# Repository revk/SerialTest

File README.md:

# ESP32-HelloWorld

Start for ESP32-RevK builds
# SerialTest

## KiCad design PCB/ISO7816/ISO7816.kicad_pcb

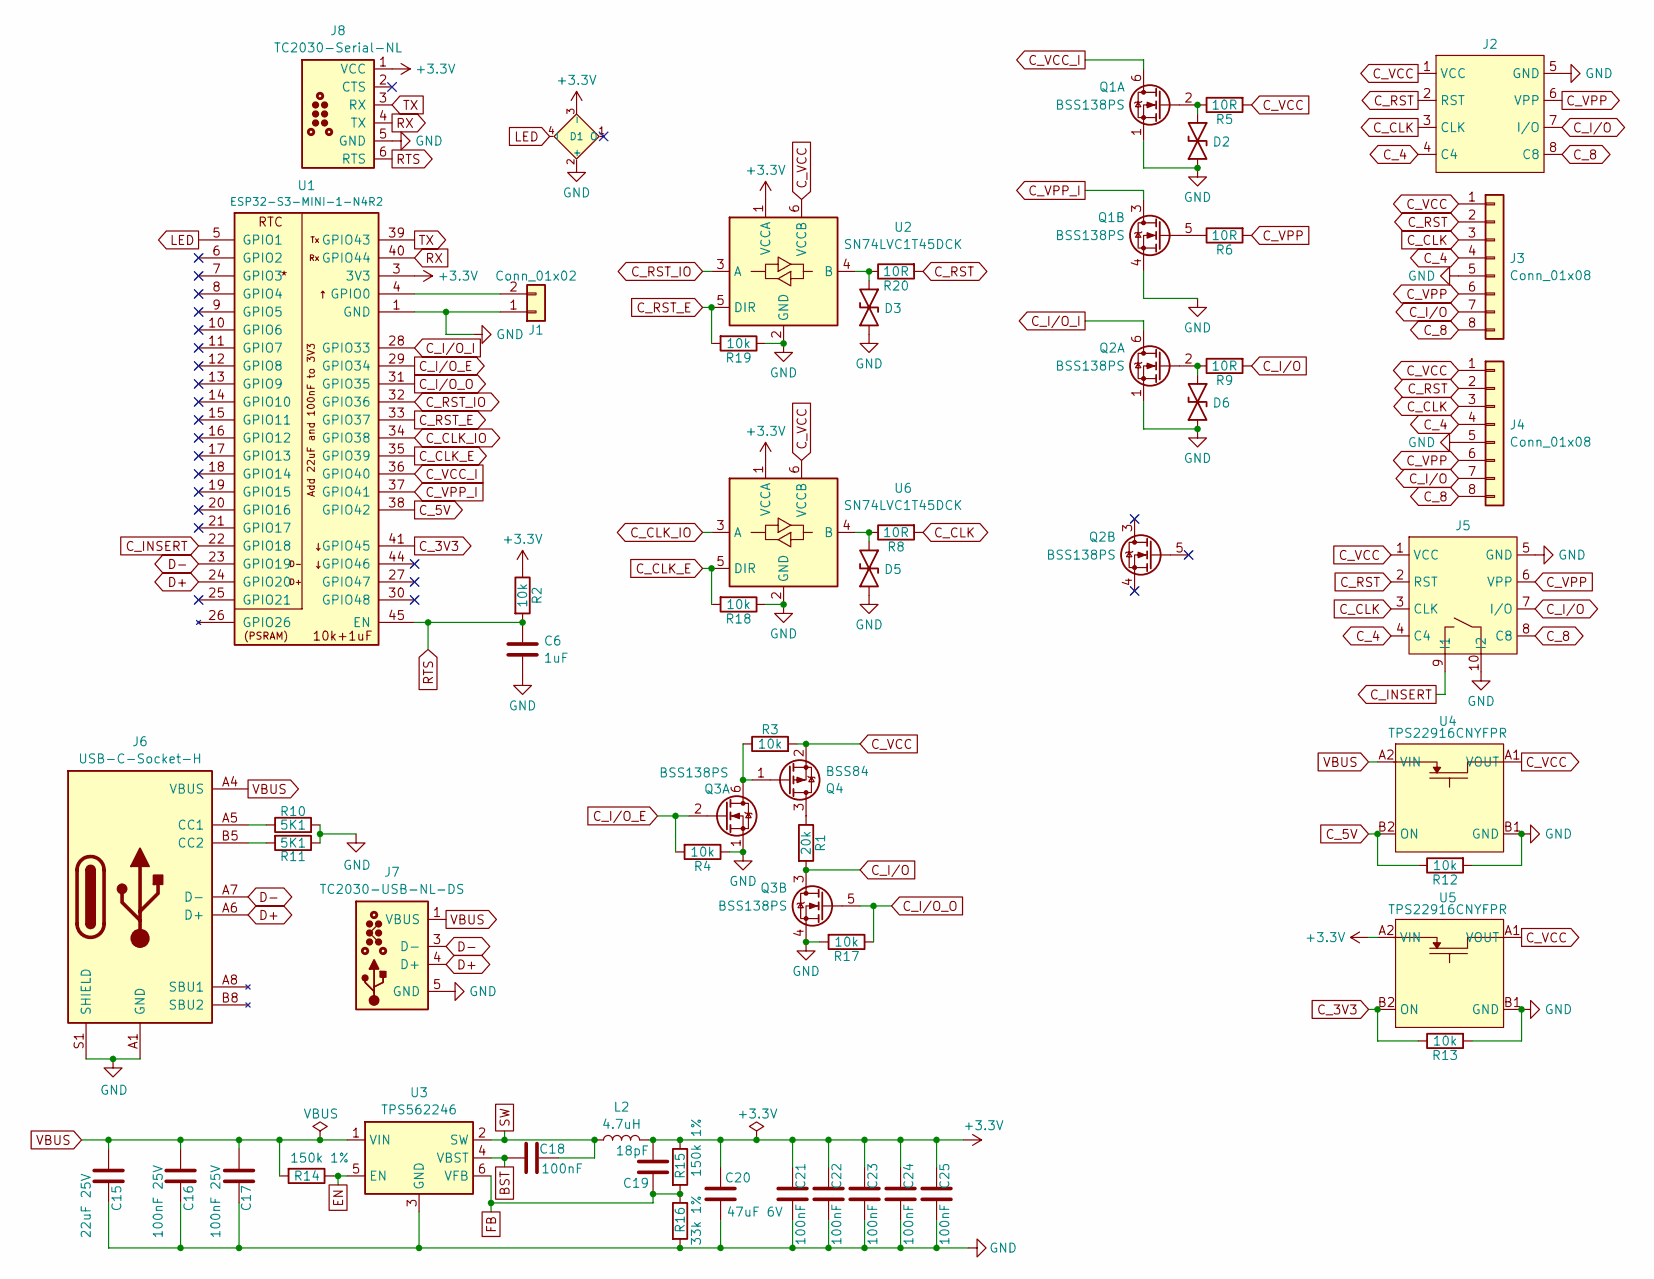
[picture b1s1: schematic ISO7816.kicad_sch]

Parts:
C6: 1uF; C_0201
C15: 22uF 25V; C_0805; MPN C45783
C16, C17: 100nF 25V; C_0402; MPN C56392
C18, C21, C22, C23, C24, C25: 100nF; C_0201; MPN C76934
C19: 18pF; C_0201; MPN C62164
C20: 47uF 6V; C_0805; MPN C16780
D1: XL-1010RGBC-WS2812B; SMD1010; MPN C5349953; LCSC Part # C5349953
D2, D3, D5, D6: DFN1006-2L; MPN C5137770; LCSC Part # C5137770
J1: Conn_01x02; AA-Pad
J2: ISO7816
J3, J4: Conn_01x08; PinHeader_1x08_P2.54mm_Vertical
J5: 7434L0825S01LF
J6: USB-C-Socket-H; MPN C709357
J7: TC2030-USB-NL-DS; Tag-Connect_TC2030-IDC-NL_2x03_P1.27mm_Vertical
J8: TC2030-Serial-NL; Tag-Connect_TC2030-IDC-NL_2x03_P1.27mm_Vertical
L2: 4.7uH; L_5x5; MPN C307876
Q1, Q2, Q3: BSS138PS; SOT-363_SC-70-6; MPN C193381; LCSC Part # C193381
Q4: BSS84; SOT-23
R1: 20k; R_0201
R2, R3, R4, R12, R13, R17, R18, R19: 10k; R_0201
R5, R6, R8, R9, R20: 10R; R_0201
R10, R11: 5K1; R_0201; MPN C274341
R14, R15: 150k 1%; R_0201; MPN C310173
R16: 33k 1%; R_0201; MPN C320835
U1: ESP32-S3-MINI-1-N4R2; ESP32-S3-MINI-1; MPN C3013941; LCSC Part # C3013941
U2, U6: SN74LVC1T45DCK; SOT-363_SC-70-6
U3: TPS562246; SOT-563; MPN C41833479
U4, U5: TPS22916CNYFPR; WCSP-4-0.78x0.78; MPN C2655476

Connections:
+3.3V: C19.2, C20.1, C21.2, C22.2, C23.2, C24.2, C25.2, D1.3 (-), J8.1 (VCC), L2.2, R2.1, R15.1, U1.3 (3V3), U2.1 (VCCA), U5.A2 (VIN), U6.1 (VCCA)
BST: C18.1, U3.4 (VBST)
C_3V3: R13.1, U1.41 (GPIO45), U5.B2 (ON)
C_4: J2.4 (C4), J3.4, J4.4, J5.4 (C4)
C_5V: R12.1, U1.38 (GPIO42), U4.B2 (ON)
C_8: J2.8 (C8), J3.8, J4.8, J5.8 (C8)
C_CLK: J2.3 (CLK), J3.3, J4.3, J5.3 (CLK), R8.2
C_CLK_E: R18.2, U1.35 (GPIO39), U6.5 (DIR)
C_CLK_IO: U1.34 (GPIO38), U6.3 (A)
C_INSERT: J5.9 (I1), U1.22 (GPIO18)
C_I/O: J2.7 (I/O), J3.7, J4.7, J5.7 (I/O), Q3.3 (SP), R1.2, R9.2
C_I/O_E: Q3.2 (GN), R4.2, U1.29 (GPIO34)
C_I/O_I: Q2.6 (DN), U1.28 (GPIO33)
C_I/O_O: Q3.5 (GP), R17.1, U1.31 (GPIO35)
C_RST: J2.2 (RST), J3.2, J4.2, J5.2 (RST), R20.2
C_RST_E: R19.2, U1.33 (GPIO37), U2.5 (DIR)
C_RST_IO: U1.32 (GPIO36), U2.3 (A)
C_VCC: J2.1 (VCC), J3.1, J4.1, J5.1 (VCC), Q4.2 (S), R3.2, R5.2, U2.6 (VCCB), U4.A1 (VOUT), U5.A1 (VOUT), U6.6 (VCCB)
C_VCC_I: Q1.6 (DN), U1.36 (GPIO40)
C_VPP: J2.6 (VPP), J3.6, J4.6, J5.6 (VPP), R6.2
C_VPP_I: Q1.3 (SP), U1.37 (GPIO41)
D+: J6.A6 (D+), J6.B6 (D+), J7.4 (D+), U1.24 (GPIO20)
D-: J6.A7 (D-), J6.B7 (D-), J7.2 (NC), J7.3 (D-), J7.6 (NC), U1.23 (GPIO19)
EN: R14.1, U3.5 (EN)
FB: C19.1, R15.2, R16.1, U3.6 (VFB)
GND: C6.2, C15.2, C16.2, C17.2, C20.2, C21.1, C22.1, C23.1, C24.1, C25.1, D1.2 (+), D2.1, D3.1, D5.1, D6.1, J1.1, J2.5 (GND), J3.5, J4.5, J5.5 (GND), J5.10 (I2), J6.A1 (GND), J6.A12 (GND), J6.B1 (GND), J6.B12 (GND), J6.S1 (SHIELD), J7.5 (GND), J8.5 (GND), Q1.1 (SN), Q1.4 (DP), Q2.1 (SN), Q3.1 (SN), Q3.4 (DP), R4.1, R10.2, R11.1, R12.2, R13.2, R16.2, R17.2, R18.1, R19.1, U1.1 (GND), U1.2 (GND), U1.42 (GND), U1.43 (GND), U1.46 (GND), U1.47 (GND), U1.48 (GND), U1.49 (GND), U1.50 (GND), U1.51 (GND), U1.52 (GND), U1.53 (GND), U1.54 (GND), U1.55 (GND), U1.56 (GND), U1.57 (GND), U1.58 (GND), U1.59 (GND), U1.60 (GND), U1.61 (GND), U1.62 (GND), U1.63 (GND), U1.64 (GND), U1.65 (GND), U2.2 (GND), U3.3 (GND), U4.B1 (GND), U5.B1 (GND), U6.2 (GND)
LED: D1.4 (I), U1.5 (GPIO1)
unnamed: J1.2, U1.4 (GPIO0)
unnamed: J6.A5 (CC1), R10.1
unnamed: J6.B5 (CC2), R11.2
unnamed: D2.2, Q1.2 (GN), R5.1
unnamed: Q1.5 (GP), R6.1
unnamed: D6.2, Q2.2 (GN), R9.1
unnamed: Q3.6 (DN), Q4.1 (G), R3.1
unnamed: Q4.3 (D), R1.1
unnamed: D3.2, R20.1, U2.4 (B)
unnamed: D5.2, R8.1, U6.4 (B)
RTS: C6.1, J8.6 (RTS), R2.2, U1.45 (EN)
RX: J8.4 (TX), U1.40 (GPIO44)
SW: C18.2, L2.1, U3.2 (SW)
TX: J8.3 (RX), U1.39 (GPIO43)
VBUS: C15.1, C16.1, C17.1, J6.A4 (VBUS), J6.A9 (VBUS), J6.B4 (VBUS), J6.B9 (VBUS), J7.1 (VBUS), R14.2, U3.1 (VIN), U4.A2 (VIN)

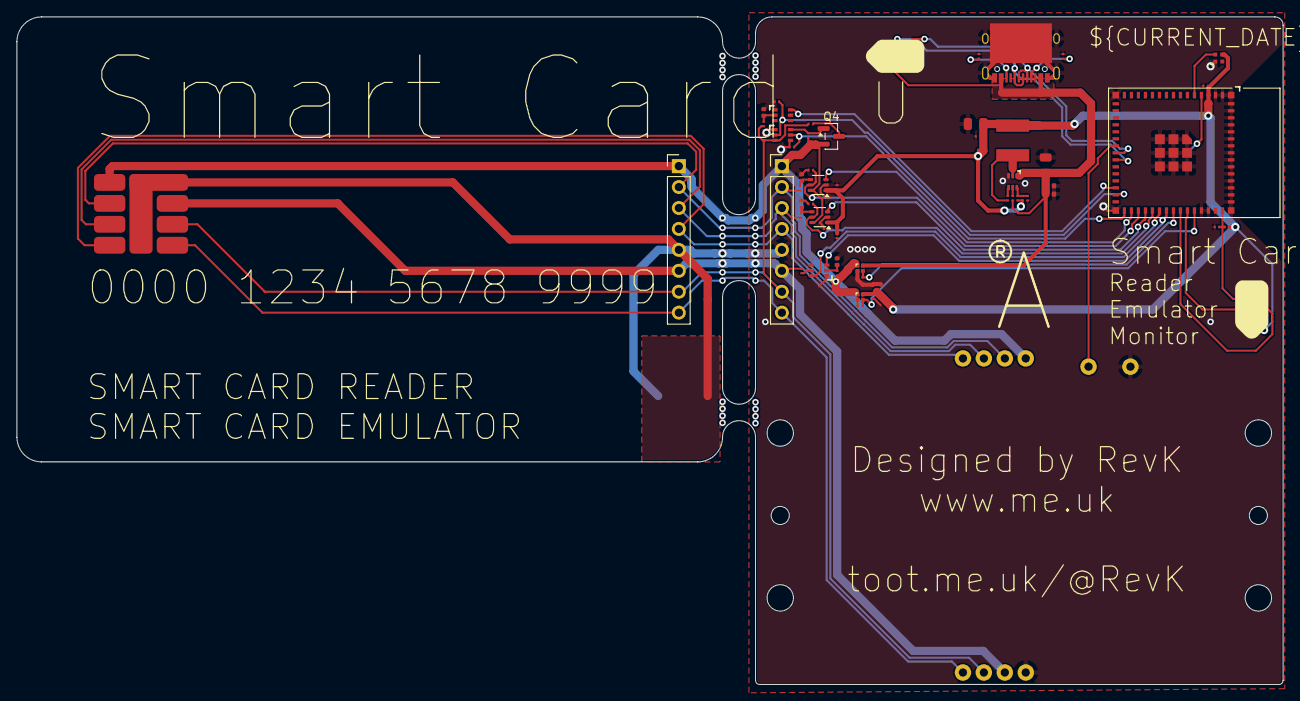
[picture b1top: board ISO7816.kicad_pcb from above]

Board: 2 copper layers, 153.6 x 81.0 mm, 55 parts (1 on the bottom side), 42 nets.

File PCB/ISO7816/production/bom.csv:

Designator,Footprint,Quantity,Value,LCSC Part #
C15,C_0805,1,22uF 25V,C45783
"C16, C17",C_0402,2,100nF 25V,C56392
"C18, C21, C22, C23, C24, C25",C_0201,6,100nF,C76934
C19,C_0201,1,18pF,C62164
C20,C_0805,1,47uF 6V,C16780
C6,C_0201,1,1uF,
D1,SMD1010,1,XL-1010RGBC-WS2812B,C5349953
"D2, D3, D5, D6",DFN1006-2L,4,~,C5137770
J6,USB-C-Socket-H,1,USB-C-Socket-H,C709357
L2,L_5x5,1,4.7uH,C307876
"Q1, Q2, Q3",SOT-363_SC-70-6,3,BSS138PS,C193381
Q4,SOT-23,1,BSS84,
R1,R_0201,1,20k,
"R10, R11",R_0201,2,5K1,C274341
"R12, R13, R17, R18, R19, R2, R3, R4",R_0201,8,10k,
"R14, R15",R_0201,2,150k 1%,C310173
R16,R_0201,1,33k 1%,C320835
"R20, R5, R6, R8, R9",R_0201,5,10R,
U1,ESP32-S3-MINI-1,1,ESP32-S3-MINI-1-N4R2,C3013941
"U2, U6",SOT-363_SC-70-6,2,SN74LVC1T45DCK,
U3,SOT-563,1,TPS562246,C41833479
"U4, U5",WCSP-4-0.78x0.78,2,TPS22916CNYFPR,C2655476

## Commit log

2025-11-13 Beta
2025-11-13 Release
2025-11-16 Schematic
2025-11-16 Ready to order
2025-11-16 Barcode
2025-11-17 Added serial
2025-11-20 Moved
